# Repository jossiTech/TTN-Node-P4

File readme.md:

# TTN-Node-P4

### LoRaWAN Node for "The Things Network" for precise mesasurement of temperature and humidity. Easy configuration of the TTN-Credentials (DevEUI, AppEUI and AppKey) with PC over FTDI-Adapter.

read more on the [Wiki](https://github.com/jossiTech/TTN-Node-P4/wiki)

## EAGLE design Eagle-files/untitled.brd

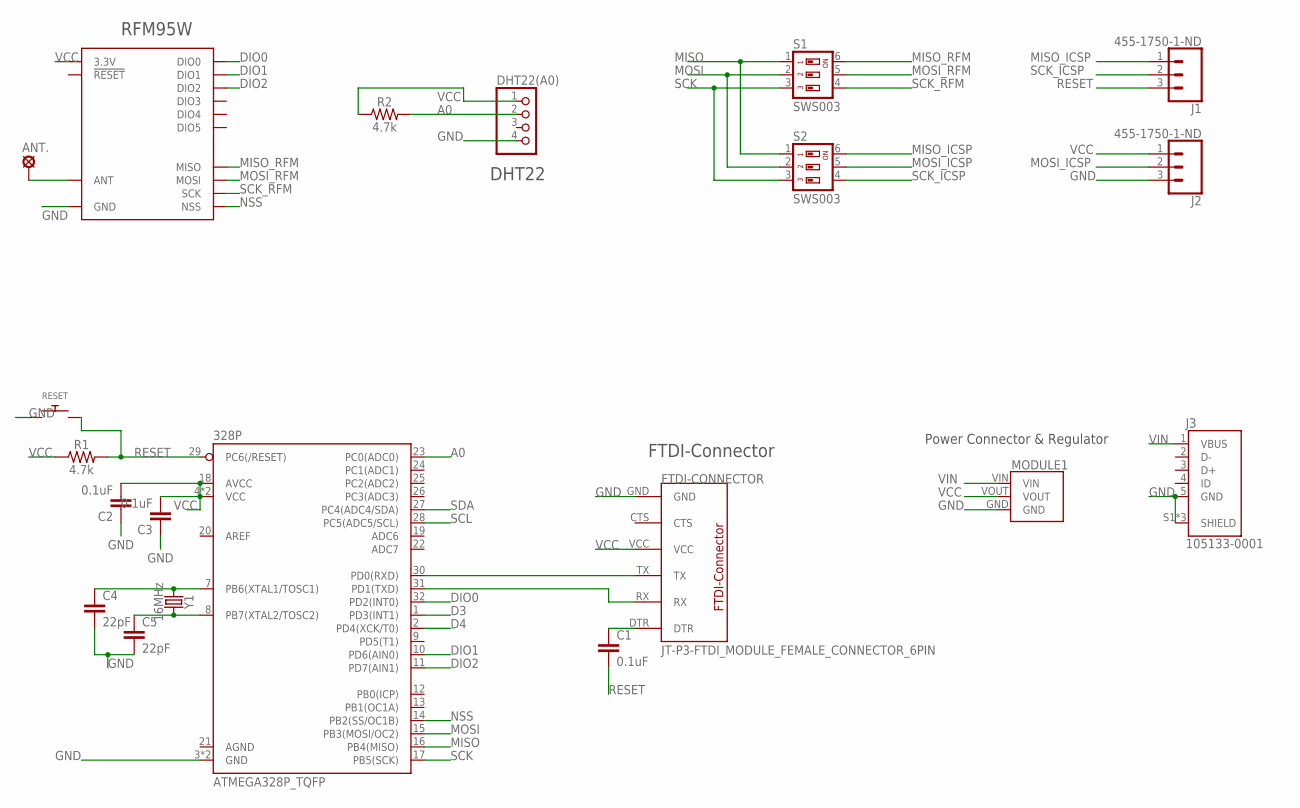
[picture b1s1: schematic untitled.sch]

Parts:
328P: ATMEGA328P_TQFP; TQFP32-08
ANT.: LSP11
C1, C2, C3: 0.1uF; 0603
C4, C5: 22pF; 0603
DHT22(A0): PINHD-1X4; 1X04
FTDI-CONNECTOR: JT-P3-FTDI_MODULE_FEMALE_CONNECTOR_6PIN
J1, J2: 455-1750-1-ND; 1X03
J3: 105133-0001; MOLEX_105133-0001
MODULE1: JT-P3-VOLTAGEREGULATOR
R1, R2: 4.7k; 0603
RESET: SWITCH_PUSHBUTTONEVQ-PE; TACT_PANA-EVQ
S1, S2: SWS003; SMS-003
U2: RFM95W; RFM95/96/97/98W
Y1: 16MHz; CRYSTAL-SMD-5X3.2-4PAD

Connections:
A0: 328P.23 (PC0(ADC0)), DHT22(A0).2, R2.2
D3: 328P.1 (PD3(INT1))
D4: 328P.2 (PD4(XCK/T0))
DIO0: 328P.32 (PD2(INT0)), U2.DIO0
DIO1: 328P.10 (PD6(AIN0)), U2.DIO1
DIO2: 328P.11 (PD7(AIN1)), U2.DIO2
GND: 328P.3 (GND), 328P.5 (GND), C2.1, C3.1, C4.2, C5.2, DHT22(A0).4, FTDI-CONNECTOR.GND, J2.3, J3.5 (GND), J3.S1 (SHIELD), J3.S2 (SHIELD), J3.S3 (SHIELD), MODULE1.GND, RESET.P$1, U2.GND@1 (GND), U2.GND@2 (GND), U2.GND@3 (GND)
MISO: 328P.16 (PB4(MISO)), S1.1, S2.1
MISO_ICSP: J1.1, S2.6
MISO_RFM: S1.6, U2.MISO
MOSI: 328P.15 (PB3(MOSI/OC2)), S1.2, S2.2
MOSI_ICSP: J2.2, S2.5
MOSI_RFM: S1.5, U2.MOSI
unnamed: ANT..MP, U2.ANT
unnamed: 328P.7 (PB6(XTAL1/TOSC1)), C4.1, Y1.1
unnamed: 328P.31 (PD1(TXD)), FTDI-CONNECTOR.RX
unnamed: 328P.30 (PD0(RXD)), FTDI-CONNECTOR.TX
unnamed: 328P.8 (PB7(XTAL2/TOSC2)), C5.1, Y1.3 (2)
unnamed: C1.1, FTDI-CONNECTOR.DTR
NSS: 328P.14 (PB2(SS/OC1B)), U2.NSS
RESET: 328P.29 (PC6(/RESET)), C1.2, J1.3, R1.2, RESET.P$2
SCK: 328P.17 (PB5(SCK)), S1.3, S2.3
SCK_ICSP: J1.2, S2.4
SCK_RFM: S1.4, U2.SCK
SCL: 328P.28 (PC5(ADC5/SCL))
SDA: 328P.27 (PC4(ADC4/SDA))
VCC: 328P.4 (VCC), 328P.6 (VCC), 328P.18 (AVCC), C2.2, C3.2, DHT22(A0).1, FTDI-CONNECTOR.VCC, J2.1, MODULE1.VOUT, R1.1, R2.1, U2.3.3V
VIN: J3.1 (VBUS), MODULE1.VIN

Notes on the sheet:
RFM95W
FTDI-Connector
DHT22
Power Connector & Regulator

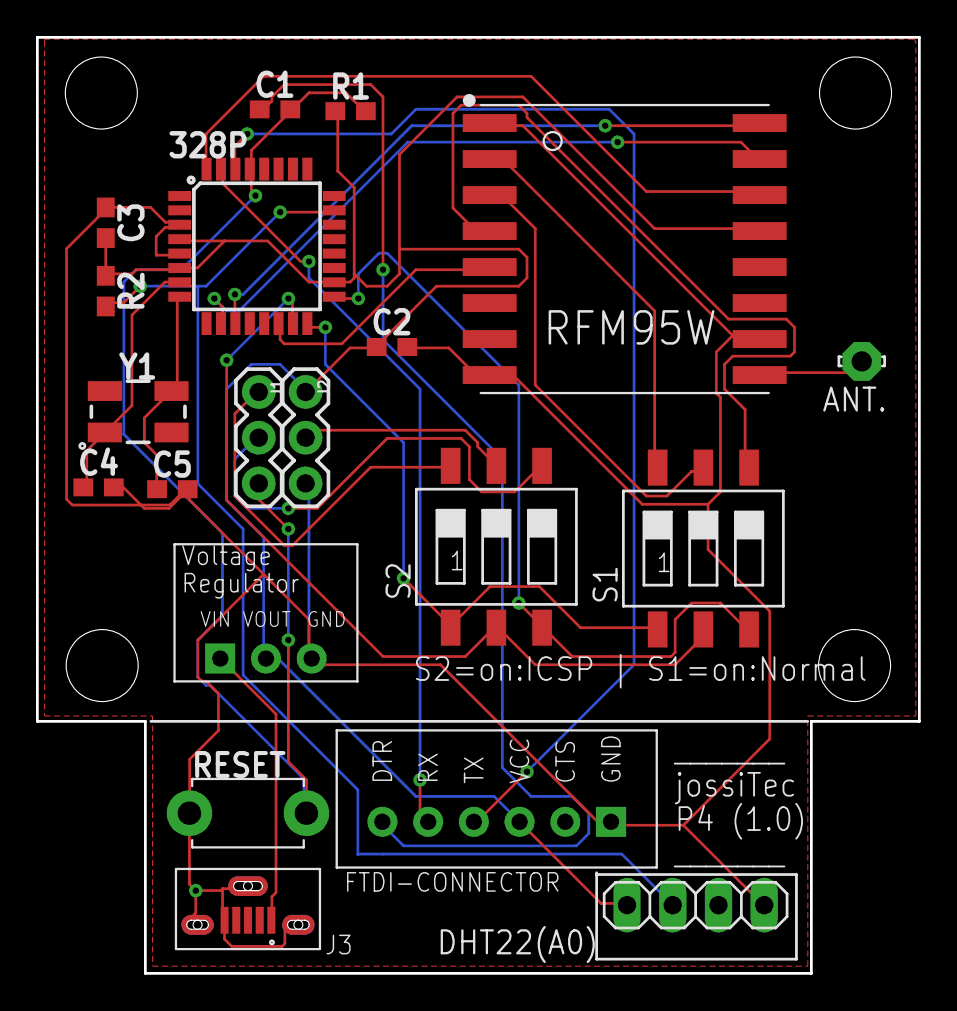
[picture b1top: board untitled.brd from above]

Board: 2 copper layers, 49.0 x 52.0 mm, 20 parts (0 on the bottom side), 24 nets.

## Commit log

2020-01-28 Create JT-P4-dht22EE
2020-01-28 Rename JT-P4-dht22EE to JT-P4-dht22EE.ino

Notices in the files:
parts and their libraries:
SparkFun-RF: Licensing: Creative Commons ShareAlike 4.0 International - https://creativecommons.org/licenses/by-sa/4.0
